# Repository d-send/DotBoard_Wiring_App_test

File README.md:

# DotBoard/BreadBoard EDA
An EDA app specifically for dot boards and Bread boards to layout components and plan/draw the wires beforehand.This comes with an DIY wire making machine designed around ESP32 Wroom32 board which you can send the drawn wires via WIFI to make them.

## Features
* Supports sending print jobs over WIFI
* 3D Wire path modelling in software
* wire cutting,bending and stripping capability
* HMI for controlling and monitering the machine
* Emergency stop button for quick stop action
* OLED display for offline printing and monitering status
* touch pads for navigating the OLED menus
* RGB LEDs for indications

## Wire making Machine
(youtube video on how to build this is coming soon)

## PCB

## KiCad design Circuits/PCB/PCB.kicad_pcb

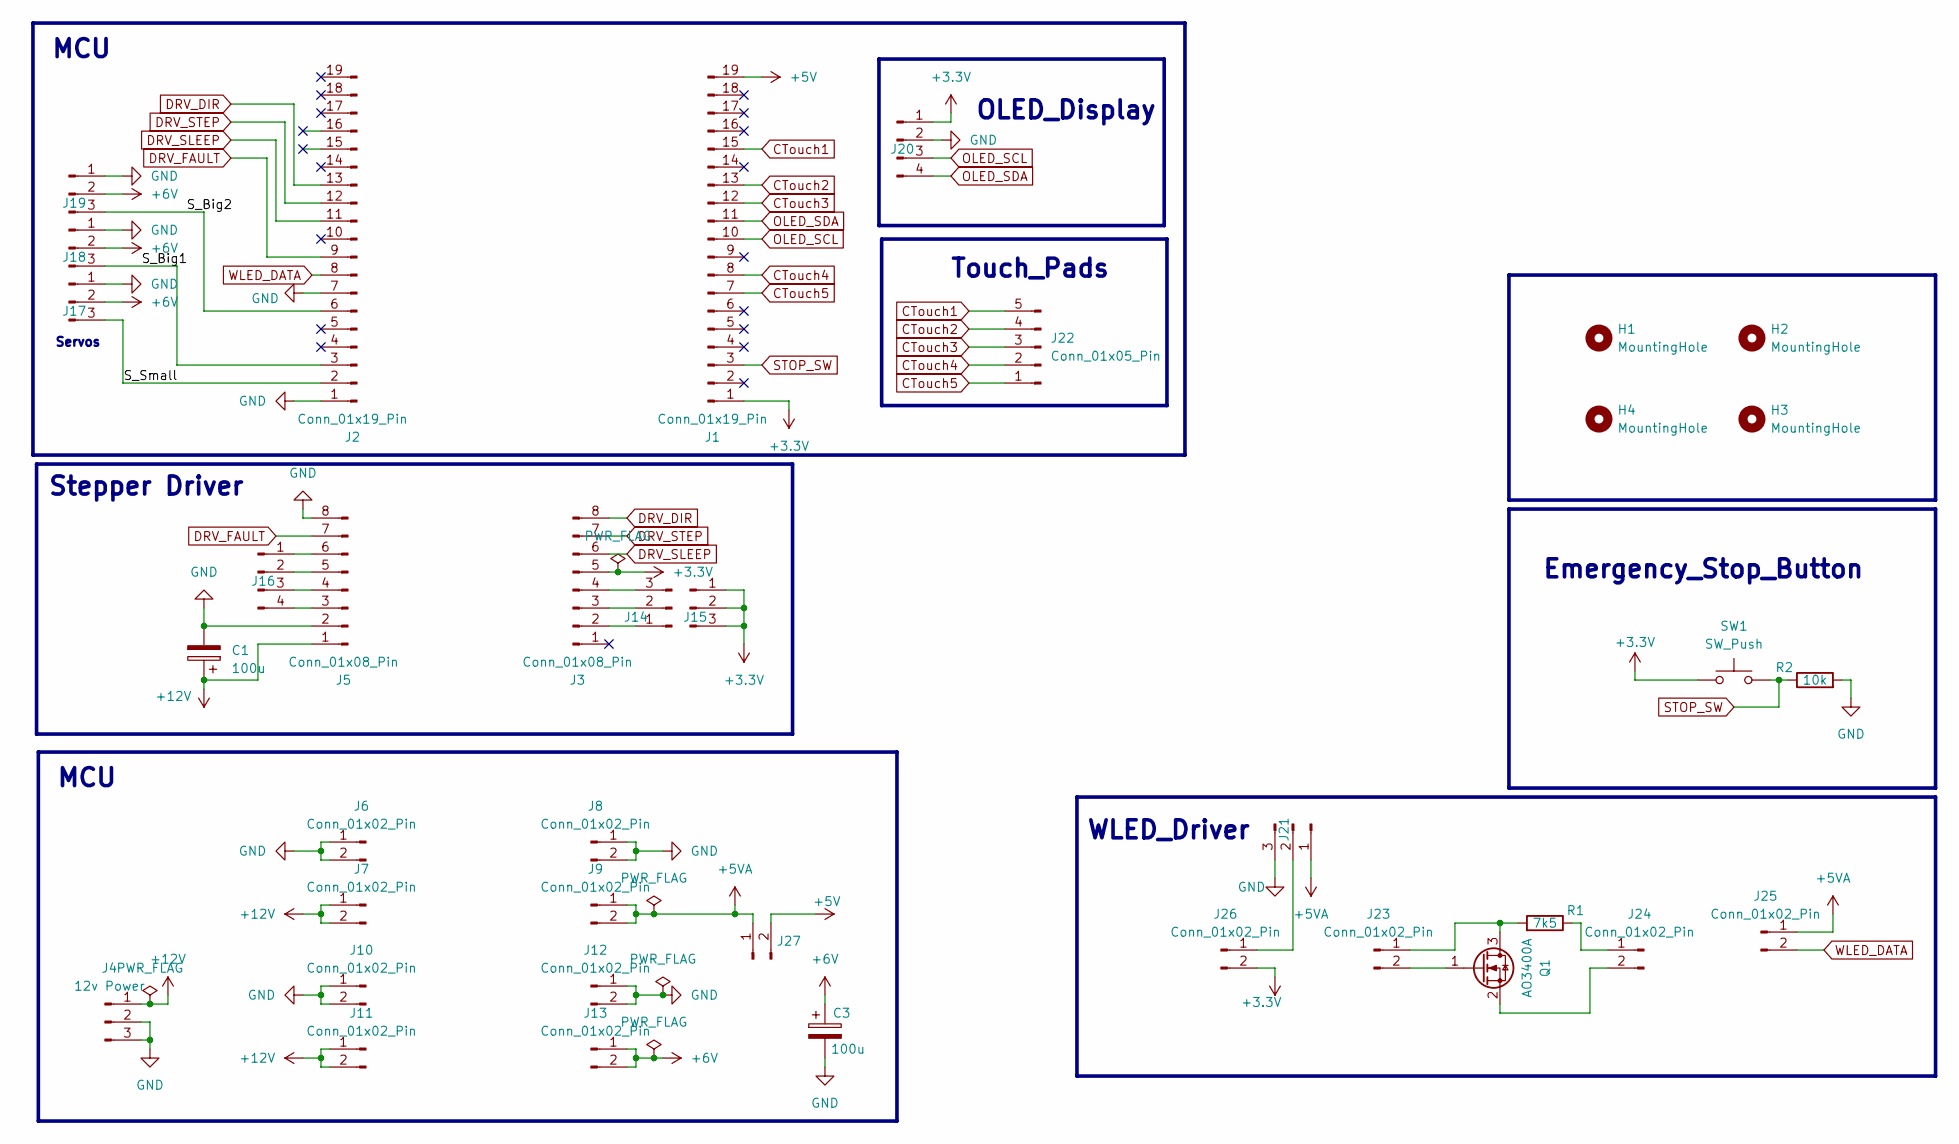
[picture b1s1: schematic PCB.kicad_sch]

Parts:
C1, C3: 100u; CP_Radial_D8.0mm_P3.50mm
H1, H2, H3, H4: MountingHole; MountingHole_3.2mm_M3
J1, J2: Conn_01x19_Pin; PinSocket_1x19_P2.54mm_Vertical
J3, J5: Conn_01x08_Pin; PinSocket_1x08_P2.54mm_Vertical
J4: 12v Power; BarrelJack_GCT_DCJ200-10-A_Horizontal
J6, J7, J8, J9, J10, J11, J12, J13, J25, J26: Conn_01x02_Pin; PinSocket_1x02_P2.54mm_Vertical
J14, J15, J17, J18, J19: Conn_01x03_Pin; PinHeader_1x03_P2.54mm_Vertical
J16: Conn_01x04_Pin; JST_XH_B4B-XH-A_1x04_P2.50mm_Vertical
J20: Conn_01x04_Pin; PinSocket_1x04_P2.54mm_Vertical
J21: Conn_01x03_Pin; JST_XH_B3B-XH-A_1x03_P2.50mm_Vertical
J22: Conn_01x05_Pin; JST_XH_B5B-XH-A_1x05_P2.50mm_Vertical
J23, J24: Conn_01x02_Pin; PinHeader_1x02_P2.54mm_Vertical
J27: Conn_01x02_Pin; PinHeader_1x02_P2.54mm_Horizontal
Q1: AO3400A; SOT-23
R1: 7k5; R_1206_3216Metric
R2: 10k; R_Axial_DIN0204_L3.6mm_D1.6mm_P7.62mm_Horizontal
SW1: SW_Push; JST_XH_B2B-XH-A_1x02_P2.50mm_Vertical

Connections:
+3.3V: J1.1, J3.5, J15.1, J15.2, J15.3, J20.1, J26.2, SW1.2
+5V: J1.19, J27.2
+5VA: J9.1, J9.2, J21.1, J25.1, J27.1
+6V: C3.1, J13.1, J13.2, J17.2, J18.2, J19.2
+12V: C1.1, J4.1, J5.1, J7.1, J7.2, J11.1, J11.2
/S_Big1: J2.3, J18.3
/S_Big2: J2.6, J19.3
/S_Small: J2.2, J17.3
CTouch1: J1.15, J22.5
CTouch2: J1.13, J22.4
CTouch3: J1.12, J22.3
CTouch4: J1.8, J22.2
CTouch5: J1.7, J22.1
DRV_DIR: J2.13, J3.8
DRV_FAULT: J2.9, J5.7
DRV_SLEEP: J2.11, J3.6
DRV_STEP: J2.12, J3.7
GND: C1.2, C3.2, J2.1, J2.7, J4.2, J4.3, J5.2, J5.8, J6.1, J6.2, J8.1, J8.2, J10.1, J10.2, J12.1, J12.2, J17.1, J18.1, J19.1, J20.2, J21.3, R2.2
unnamed: J3.2, J14.1
unnamed: J3.3, J14.2
unnamed: J3.4, J14.3
unnamed: J5.6, J16.1
unnamed: J5.5, J16.2
unnamed: J5.4, J16.3
unnamed: J5.3, J16.4
unnamed: J21.2, J26.1
unnamed: J23.1, Q1.3 (D), R1.2
unnamed: J23.2, Q1.1 (G)
unnamed: J24.1, R1.1
unnamed: J24.2, Q1.2 (S)
OLED_SCL: J1.10, J20.3
OLED_SDA: J1.11, J20.4
STOP_SW: J1.3, R2.1, SW1.1
WLED_DATA: J2.8, J25.2

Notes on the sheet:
Stepper Driver
WLED_Driver
Servos
OLED_Display
Touch_Pads
Emergency_Stop_Button
MCU

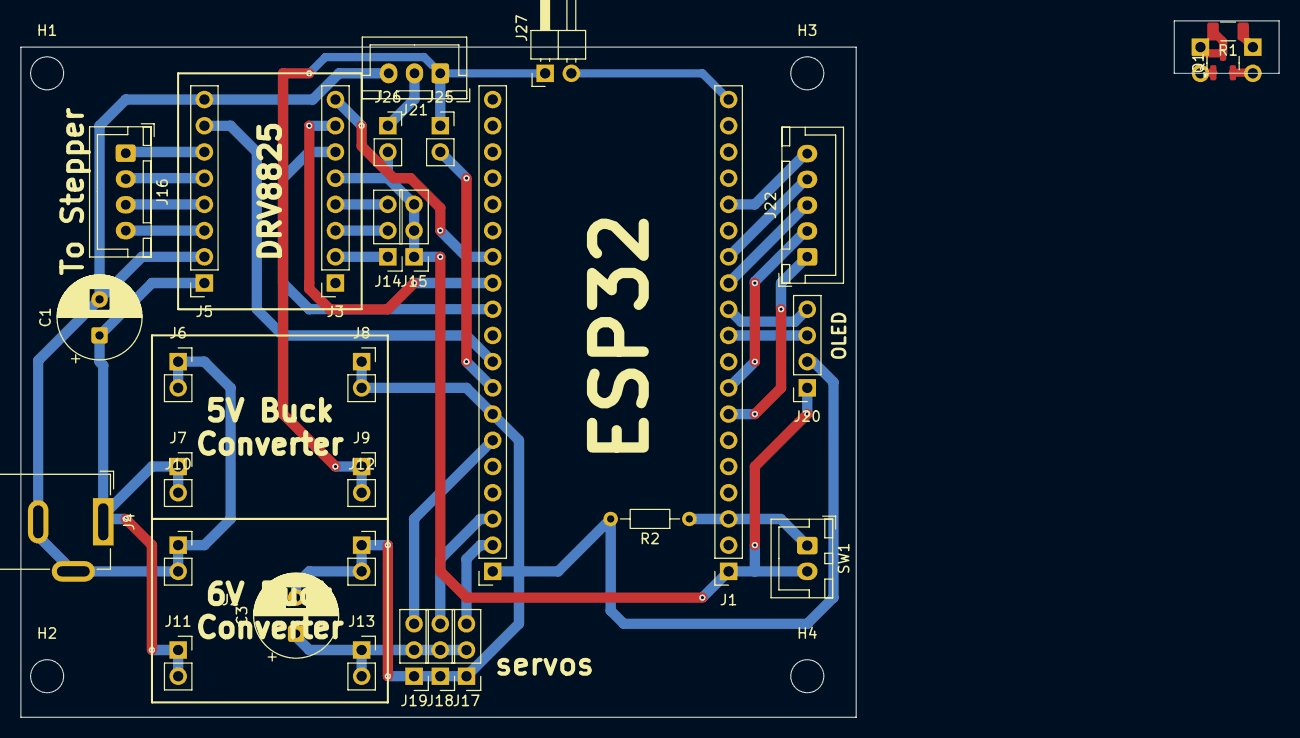
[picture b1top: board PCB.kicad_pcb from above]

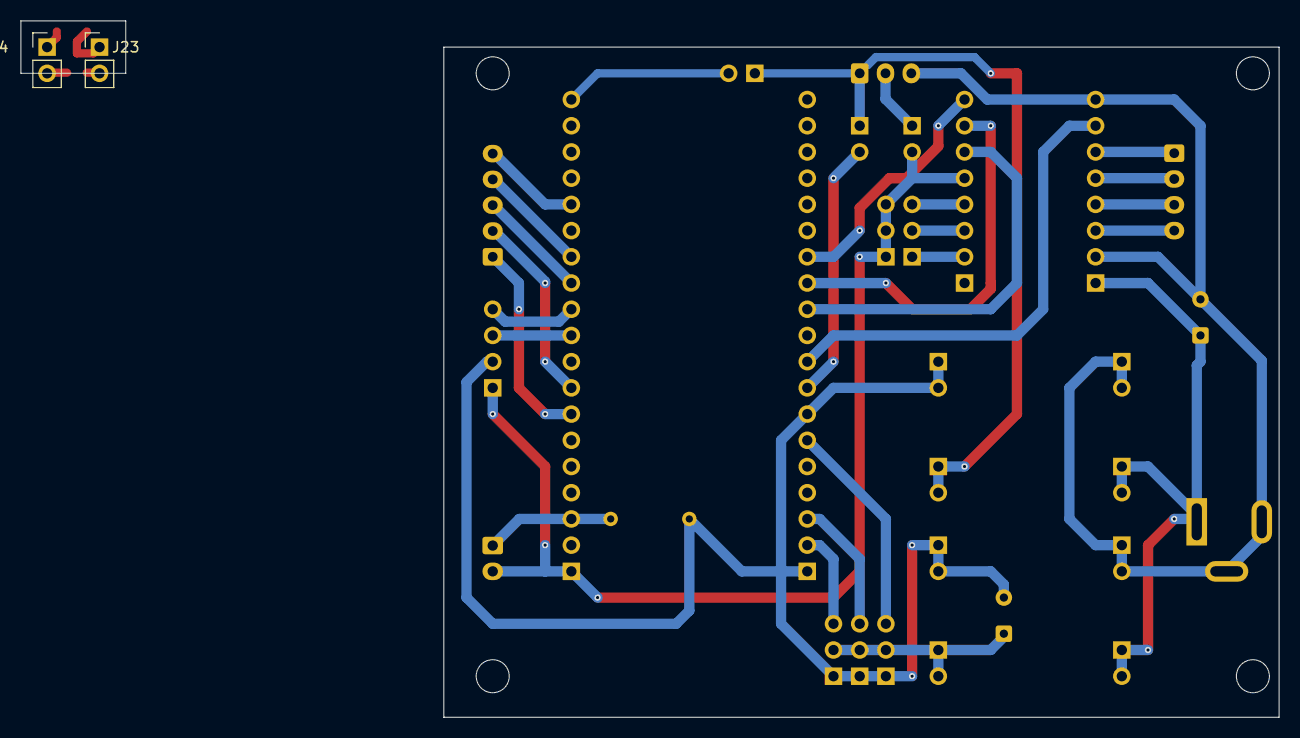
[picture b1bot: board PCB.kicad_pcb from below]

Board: 2 copper layers, 121.9 x 67.5 mm, 37 parts (2 on the bottom side), 34 nets.

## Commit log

2025-09-26 sending msgs to ESP32 via WIFI implemented.
    The code for sending messages over wifi from the computer to ESP32 via the router was implemted.The Arduino
    sketch contains the code for connecting to the router and printing the recieved messages.
2025-09-26 Added raylib to the project
2025-09-26 fixed collision with raylib and win32 api
2025-09-26 Working raylib window was created.
2025-09-26 Dot board created on the window.
2025-09-26 PinHole detection when mouse hovering implemented.
2025-09-26 Coding basic wire drawing.
2025-09-26 Added A,E,X keys for adding,extending,terminating wires.
2025-09-26 Wire selection via clicking on them was implemented.
2025-09-26 Selected Wire deletion using Delete key added.
2025-09-26 Added basic file storing for the wire data.
2025-09-26 Sending Wire Data to ESP32 over wifi code tested.
2025-09-27 wire segment lengths and the relative angles between them were calculated.
2025-10-06 Added Dropdown textbox for inserting/selecting IP and Port.
2025-10-07 Added App class for refactoring the application code.
2025-10-07 Refactored existing code to the App class and resolved all errors.
2025-10-07 Included ws2_32.lib file in the premake files.
2025-10-07 Added app class implementation under the DBW namespace.
2025-10-07 Refactored code relevent to Rendering Board & Hovering.
2025-10-08 Moved the Dropdownmenu into Overlay function.
2025-10-12 Changed save file locations to Folders GCodes and WireFiles.
2025-11-08 refactored project save and Gcode generate functions.
2026-03-10 Add readme
2026-03-10 3D Files & Circuit Files Added
2026-03-10 README updated
